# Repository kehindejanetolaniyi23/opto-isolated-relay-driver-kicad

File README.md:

# Opto-Isolated Relay Driver PCB Design in KiCad

This repository contains a complete KiCad PCB design project for an opto-isolated relay driver circuit. The board is designed to allow a low-voltage microcontroller control signal to switch an external load through a relay while using optocoupler isolation between the control input and relay driver stage.

## Project Overview

The circuit demonstrates a practical embedded electronics interface commonly used in automation, control systems, and microcontroller-based switching applications.

The design includes:

* Microcontroller control input
* PC817 optocoupler isolation stage
* NPN transistor relay driver
* 5V SPDT relay
* Flyback diode protection
* Input indicator LED
* Relay status LED
* 5V power input terminal
* COM, NO, and NC relay output terminal
* Fully routed PCB layout
* Clean DRC result
* 3D PCB view
* Gerber fabrication outputs

## Design Purpose

The purpose of this project is to demonstrate a complete KiCad PCB design workflow, from schematic capture to PCB layout and fabrication output generation.

The relay driver circuit is useful for switching external devices using a microcontroller signal while keeping the control side separated from the relay-driving stage through optocoupler isolation.

## Tools Used

* KiCad
* KiCad Schematic Editor
* KiCad PCB Editor
* KiCad 3D Viewer
* KiCad Gerber Viewer

## Main Circuit Blocks

### 1. Control Input Stage

The microcontroller control input is connected through a resistor and input indicator LED. This section provides a visual indication when a control signal is applied.

### 2. Optocoupler Isolation Stage

A PC817 optocoupler is used to provide electrical separation between the microcontroller input side and the relay driver side. This improves protection and reduces direct electrical coupling between the two sections.

### 3. Transistor Relay Driver Stage

An NPN transistor is used to drive the relay coil. The transistor allows the low-current control signal from the optocoupler output to control the higher current required by the relay coil.

### 4. Flyback Protection

A 1N4007 diode is connected across the relay coil to protect the transistor from reverse voltage spikes generated when the relay coil turns off.

### 5. Relay Output Stage

The relay output is routed to a three-pin terminal block with COM, NO, and NC connections. This allows the board to switch an external load depending on the relay state.

## Project Files

The repository includes:

* `.kicad_pro` — KiCad project file
* `.kicad_sch` — schematic design file
* `.kicad_pcb` — routed PCB layout file
* `gerbers/` — exported PCB fabrication files
* `Screenshots/` — schematic, layout, DRC, 3D view, and Gerber verification screenshots

## Verification

The PCB layout was checked using KiCad Design Rules Checker.

Result:

* Violations: 0
* Unconnected items: 0
* Errors: 0
* Warnings: 0

This confirms that the board layout is fully routed and passes the KiCad DRC check.

## Fabrication Output

The `gerbers/` folder contains the exported Gerber and drill files required for PCB fabrication.

Included manufacturing layers:

* Front copper
* Back copper
* Front silkscreen
* Back silkscreen
* Front solder mask
* Back solder mask
* Board outline
* Drill files

## Status

Completed portfolio PCB design project.

The project demonstrates schematic capture, footprint assignment, PCB routing, DRC verification, 3D board inspection, and Gerber file export using KiCad.

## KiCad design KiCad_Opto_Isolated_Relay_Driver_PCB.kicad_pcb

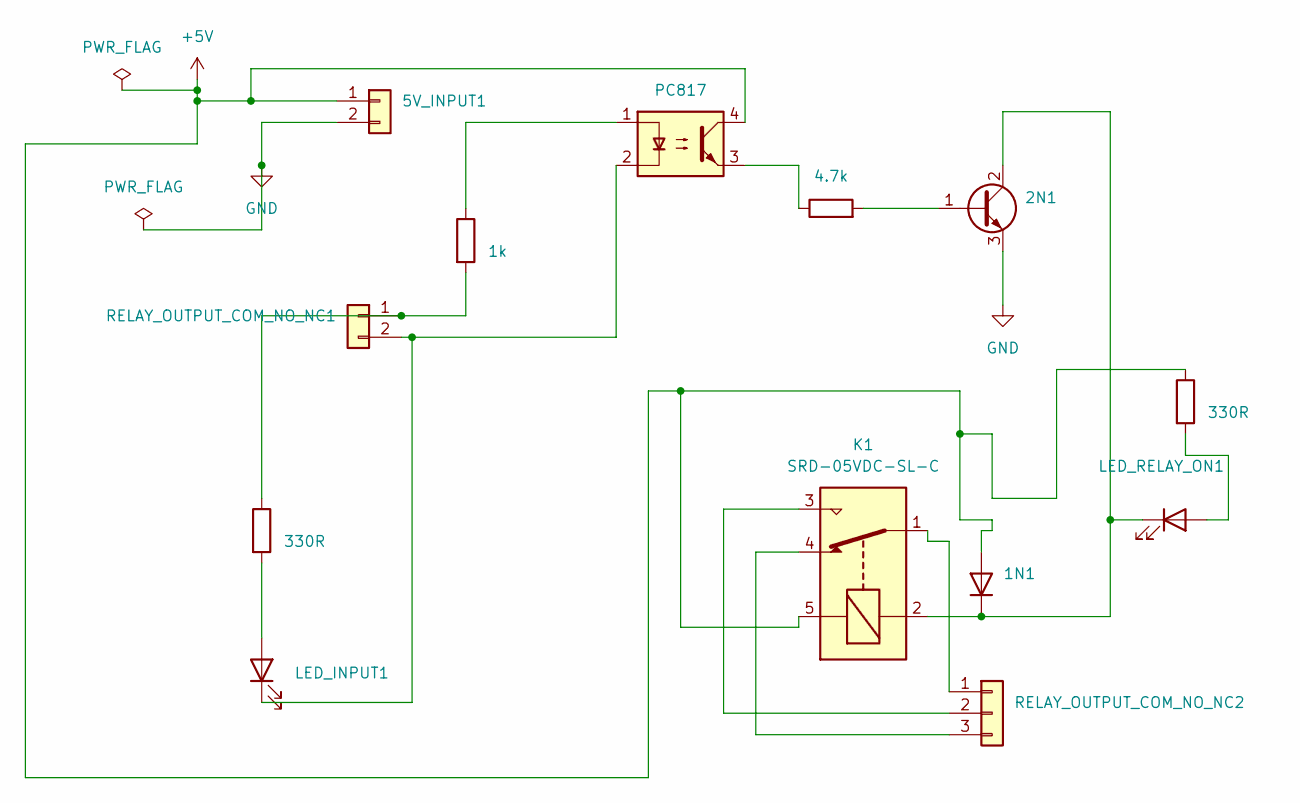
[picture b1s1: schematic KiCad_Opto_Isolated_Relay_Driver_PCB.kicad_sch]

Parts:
1N1: D; D_DO-41_SOD81_P10.16mm_Horizontal
2N1: Q_NPN_BCE; TO-92_Inline
5V_INPUT1: Conn_01x02; TerminalBlock_Phoenix_MKDS-1,5-2-5.08_1x02_P5.08mm_Horizont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
K1: SRD-05VDC-SL-C; Relay_SPDT_SANYOU_SRD_Series_Form_C
LED_INPUT1: LED; LED_D5.0mm
LED_RELAY_ON1: LED; LED_D5.0mm
Optocoupler1: PC817; DIP-4_W7.62mm
R1, R4: 330R; R_Axial_DIN0207_L6.3mm_D2.5mm_P10.16mm_Horizontal
R2: 1k; R_Axial_DIN0207_L6.3mm_D2.5mm_P10.16mm_Horizontal
R3: 4.7k; R_Axial_DIN0207_L6.3mm_D2.5mm_P10.16mm_Horizontal
RELAY_OUTPUT_COM_NO_NC1: Conn_01x02; PinHeader_1x02_P2.54mm_Vertical
RELAY_OUTPUT_COM_NO_NC2: Conn_01x03; TerminalBlock_Phoenix_MKDS-1,5-3-5.08_1x03_P5.08mm_Horizont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

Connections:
+5V: 1N1.2 (A), 5V_INPUT1.1, K1.5, Optocoupler1.4, R4.1
GND: 2N1.3 (E), 5V_INPUT1.2
unnamed: 1N1.1 (K), 2N1.2 (C), K1.2, LED_RELAY_ON1.1 (K)
unnamed: 2N1.1 (B), R3.2
unnamed: LED_INPUT1.2 (A), R1.2
unnamed 5: LED_INPUT1.1 (K), Optocoupler1.2, RELAY_OUTPUT_COM_NO_NC1.2; also elsewhere on the board
unnamed: LED_RELAY_ON1.2 (A), R4.2
unnamed: Optocoupler1.1, R2.1
unnamed: Optocoupler1.3, R3.1
unnamed 9: R1.1, R2.2, RELAY_OUTPUT_COM_NO_NC1.1; also elsewhere on the board
unnamed: K1.1, RELAY_OUTPUT_COM_NO_NC2.1
unnamed: K1.3, RELAY_OUTPUT_COM_NO_NC2.2
unnamed: K1.4, RELAY_OUTPUT_COM_NO_NC2.3

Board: 2 copper layers, 13 parts (0 on the bottom side), 13 nets, no tracks yet.

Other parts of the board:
MCU_CONTROL_INPUT: Conn_01x02; PinHeader_1x02_P2.54mm_Vertical

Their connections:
unnamed 5: MCU_CONTROL_INPUT.2; also elsewhere on the board
unnamed 9: MCU_CONTROL_INPUT.1; also elsewhere on the board

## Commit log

2026-06-25 Add complete KiCad opto-isolated relay driver PCB project
2026-06-25 Add screenshots and Gerber fabrication outputs
2026-06-25 Revise README for Opto-Isolated Relay Driver project
    Updated README to provide detailed project overview, design purpose, tools used, and verification results for the Opto-Isolated Relay Driver PCB design in KiCad.
2026-06-25 Delete screenshots from README.md
    Removed screenshots section from the README.
